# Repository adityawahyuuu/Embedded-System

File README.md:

# Kumpulan Project Embedded-System

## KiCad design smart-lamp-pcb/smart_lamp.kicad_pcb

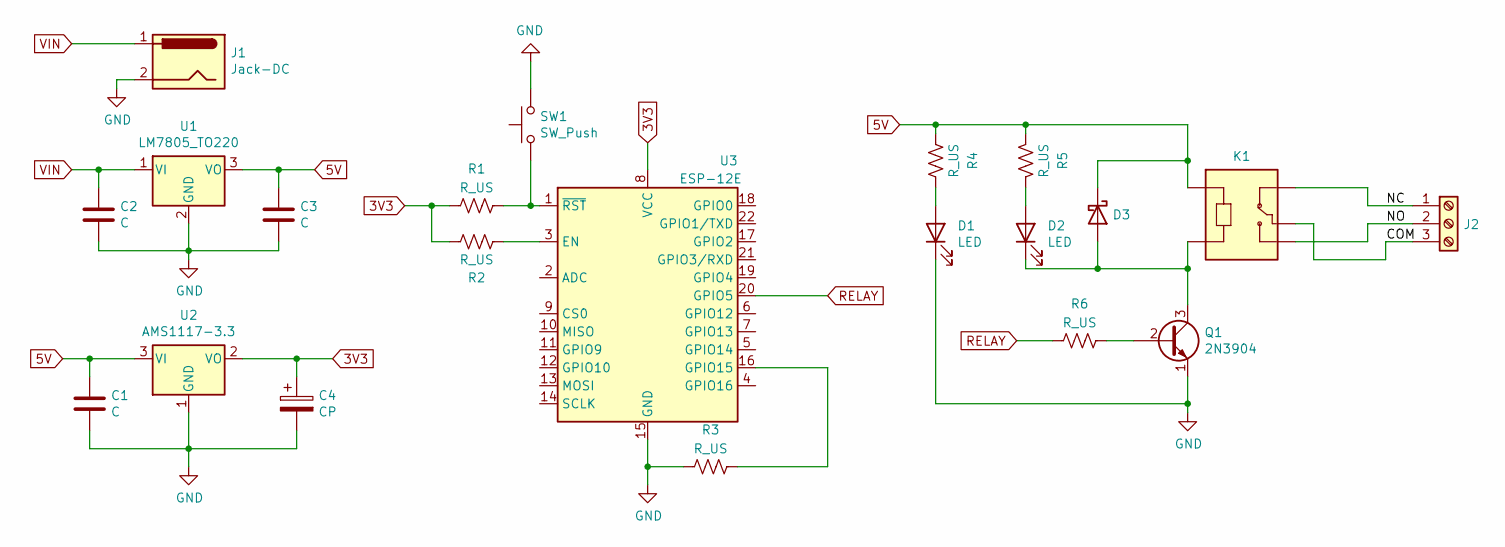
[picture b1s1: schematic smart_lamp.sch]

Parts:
C1, C2, C3: C; CP_Radial_Tantal_D5.0mm_P2.50mm
C4: CP; CP_Radial_D5.0mm_P2.50mm
D1, D2: LED; LED_D3.0mm
D3: D_Schottky; D_DO-35_SOD27_P7.62mm_Horizontal
J1: Jack-DC; BarrelJack_Horizontal
J2: Screw_Terminal_01x03; TerminalBlock_bornier-3_P5.08mm
K1: SRD-05VDC-SL-C; RELAY_SRD-05VDC-SL-C
Q1: 2N3904; TO-92_Inline
R1, R2, R3, R4, R5, R6: R_US; R_Axial_DIN0207_L6.3mm_D2.5mm_P7.62mm_Horizontal
SW1: SW_Push; SW_PUSH_6mm
U1: LM7805_TO220; TO-220-3_Vertical
U2: AMS1117-3.3; SOT-223-3_TabPin2
U3: ESP-12E

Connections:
3V3: C4.1, R1.2, R2.2, U2.2 (VO), U3.8 (VCC)
5V: C1.1, C3.1, D3.1 (K), K1.A2, R4.2, R5.1, U1.3 (VO), U2.3 (VI)
/COM: J2.3, K1.COM
/NC: J2.1, K1.NC
/NO: J2.2, K1.NO
GND: C1.2, C2.2, C3.2, C4.2, D1.1 (K), J1.2, Q1.1 (E), R3.2, SW1.2, U1.2 (GND), U2.1 (GND), U3.15 (GND)
unnamed: D1.2 (A), R4.1
unnamed: D2.1 (K), D3.2 (A), K1.A1, Q1.3 (C)
unnamed: D2.2 (A), R5.2
unnamed: Q1.2 (B), R6.1
unnamed: R1.1, SW1.1, U3.1 (~RST)
unnamed: R2.1, U3.3 (EN)
unnamed: R3.1, U3.16 (GPIO15)
RELAY: R6.2, U3.20 (GPIO5)
VIN: C2.1, J1.1, U1.1 (VI)

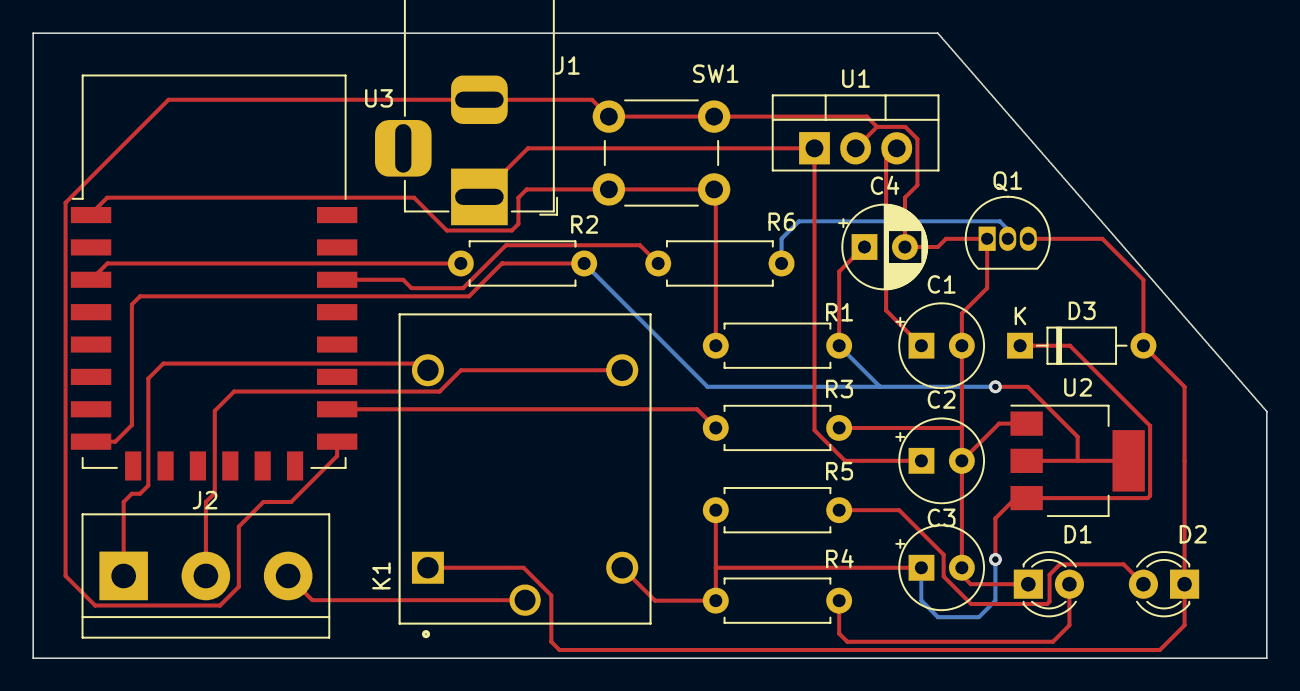
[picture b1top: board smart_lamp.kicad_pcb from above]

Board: 2 copper layers, 76.2 x 38.6 mm, 21 parts (0 on the bottom side), 15 nets.
